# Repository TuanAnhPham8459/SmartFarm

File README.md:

<h1 align="center">Smart Farm</h1>

<p align="center">
  <b>Real-time farm monitoring: Raspberry Pi sensors → Cloud Firestore → Android app with live alerts</b>
</p>

---

## Overview

Smart Farm is an end-to-end IoT system that helps growers watch their environment remotely.
A Raspberry Pi 4 with a **custom sensor PCB** measures temperature, humidity, pressure, air
quality, light, and produce color, reads RFID tags, and shows status on a small OLED. Every
reading is uploaded to **Cloud Firestore**, and an **Android app** displays the data live,
charts history, and sends notifications when conditions go out of range.

Built by a team of four as our Computer Engineering Technology capstone at Humber College.

## Features

**Hardware & firmware (Raspberry Pi 4)**
- 🌡️ **Environment:** temperature, humidity, pressure, and gas/air quality (BME688)
- 💡 **Light:** ambient lux (VEML7700)
- 🍅 **Produce color classification:** GREEN / YELLOW / BROWN / RED with a calibration mode (OPT4048)
- 🏷️ **RFID:** ID-12LA reader on an I²C carrier board
- 🖥️ **On-device display:** SSD1305 128×32 OLED status screen, plus a GPIO LED indicator
- ☁️ **Cloud upload:** timestamped readings written to Firestore
- 🧵 **Reliable I²C:** one shared bus with a single lock across all devices, so threads never collide

**Android app**
- 🔐 Email and Google sign-in (Firebase Authentication), account profile with photo
- 📊 Live dashboard of the latest sensor readings
- 📈 History and analytics graphs (MPAndroidChart)
- 🚨 Threshold alerts with push notifications and a cooldown so you aren't spammed
- 🎛️ Control panel for device actions (irrigation pump, fan, light, auto mode)
- 🌙 Light and dark themes, French translation, unit switching, landscape layouts
- 💬 In-app feedback and help pages
- ✅ Unit tests (JUnit, Robolectric) and UI tests (Espresso)

## How it works

```mermaid
flowchart LR
    subgraph PI["Raspberry Pi 4 + custom PCB"]
        S1[BME688<br/>env + air quality]
        S2[VEML7700<br/>light]
        S3[OPT4048<br/>color]
        S4[ID-12LA<br/>RFID]
        FW[Python firmware<br/>shared I²C bus]
        OLED[SSD1305 OLED<br/>+ GPIO LED]
        S1 & S2 & S3 & S4 -->|I²C / Qwiic| FW
        FW --> OLED
    end
    FW -->|readings| FS[(Cloud Firestore)]
    FS -->|live updates| APP[Android app]
    APP -->|controls| FS
    APP --> N[Push alerts]
```

Firestore layout used by the firmware and the app:

```
sensor_data/{deviceId}/readings/{timestamp}   ← sensor readings from the Pi
devices/…                                      ← registered devices and controls
history/…                                      ← alert history
feedback/…                                     ← in-app feedback
```

## Tech stack

| Layer | Tools |
|---|---|
| Mobile app | Java, Android SDK (min SDK 31), Material Components, MPAndroidChart, Glide |
| Cloud | Firebase Authentication, Cloud Firestore, Firebase Storage |
| Firmware | Python 3, Adafruit Blinka / CircuitPython libraries, smbus2, Pillow |
| Hardware | Raspberry Pi 4, BME688, VEML7700, OPT4048, ID-12LA RFID, SSD1305 OLED, Qwiic |
| Design | KiCad (custom PCB), laser-cut enclosure (SVG) |
| Testing | JUnit, Robolectric, Espresso |

## Repository structure

```
SmartFarm/
├── SmartFarmModule/      Android app (Java)
│   └── src/main/java/ca/iot/innovators/smart/farm/
│       ├── firestore/    data managers for sensors, devices, alerts
│       ├── ui/           dashboard, control panel, settings, help, feedback
│       ├── alert/        alert list and notifications
│       ├── history/      analytics graphs
│       └── login/ signup/ profile/
├── hardware/
│   ├── firmware/         Raspberry Pi Python scripts
│   ├── pcb/              KiCad schematic and board files
│   └── *.svg, *.docx     enclosure drawings, bill of materials, build reports
├── docs/                 project deliverables 1–5 (PDF)
├── system/               weekly course status reports
└── privacy-policy/       app privacy policy and account deletion pages
```

## Getting started

### Raspberry Pi firmware

```bash
# 1. Enable I²C:  sudo raspi-config → Interface Options → I2C
# 2. Install dependencies
pip3 install adafruit-blinka adafruit-circuitpython-bme680 \
             adafruit-circuitpython-veml7700 adafruit-circuitpython-ssd1305 \
             adafruit-circuitpython-opt4048 smbus2 pillow google-cloud-firestore
# 3. Check that the sensors are detected
i2cdetect -y 1        # expect 0x10, 0x15, 0x3C, 0x77 (and the OPT4048)
# 4. Run
cd hardware/firmware
python3 pcb_sensors_color_oled_firestore.py             # everything
python3 pcb_sensors_color_oled_firestore.py calibrate   # color calibration only
```

You'll need a Firebase service account key on the Pi for the Firestore upload.

### Android app

1. Open the project in **Android Studio**.
2. Add your own `google-services.json` from a Firebase project to `SmartFarmModule/`.
3. Build and run on a device or emulator running Android 12 (API 31) or later.

## Project documents

- 📄 [Deliverables 1–5](docs/)
- 🪧 [Project poster](hardware/SmartFarm_poster.pdf)
- 🔌 [PCB design files](hardware/pcb/)
- 🧾 [Bill of materials](hardware/Smart%20Farm%20-%20BoM.docx)

## Team

| Member | Focus |
|---|---|
| Chau Vi Cuong Nguyen | Hardware, firmware, PCB design |
| Hoang Tran | Hardware, firmware, RFID reader |
| Truong An Nguyen | Hardware, firmware, OPT4048 color sensing |
| **Tuan Anh Pham** | Hardware, firmware, sensor integration |

### My contribution (Tuan Anh Pham)
- Merged the PCB sensor script and the OPT4048 color-classification script into one program
  (`pcb_sensors_color_oled_firestore.py`) that drives every sensor, the OLED, and the Firestore upload
- Diagnosed and fixed a bug where the RFID reader status stored in Firestore didn't match the reader's real state
- Wrote my individual hardware report with build instructions for the Raspberry Pi platform

> This repository is my fork of the team's capstone project.

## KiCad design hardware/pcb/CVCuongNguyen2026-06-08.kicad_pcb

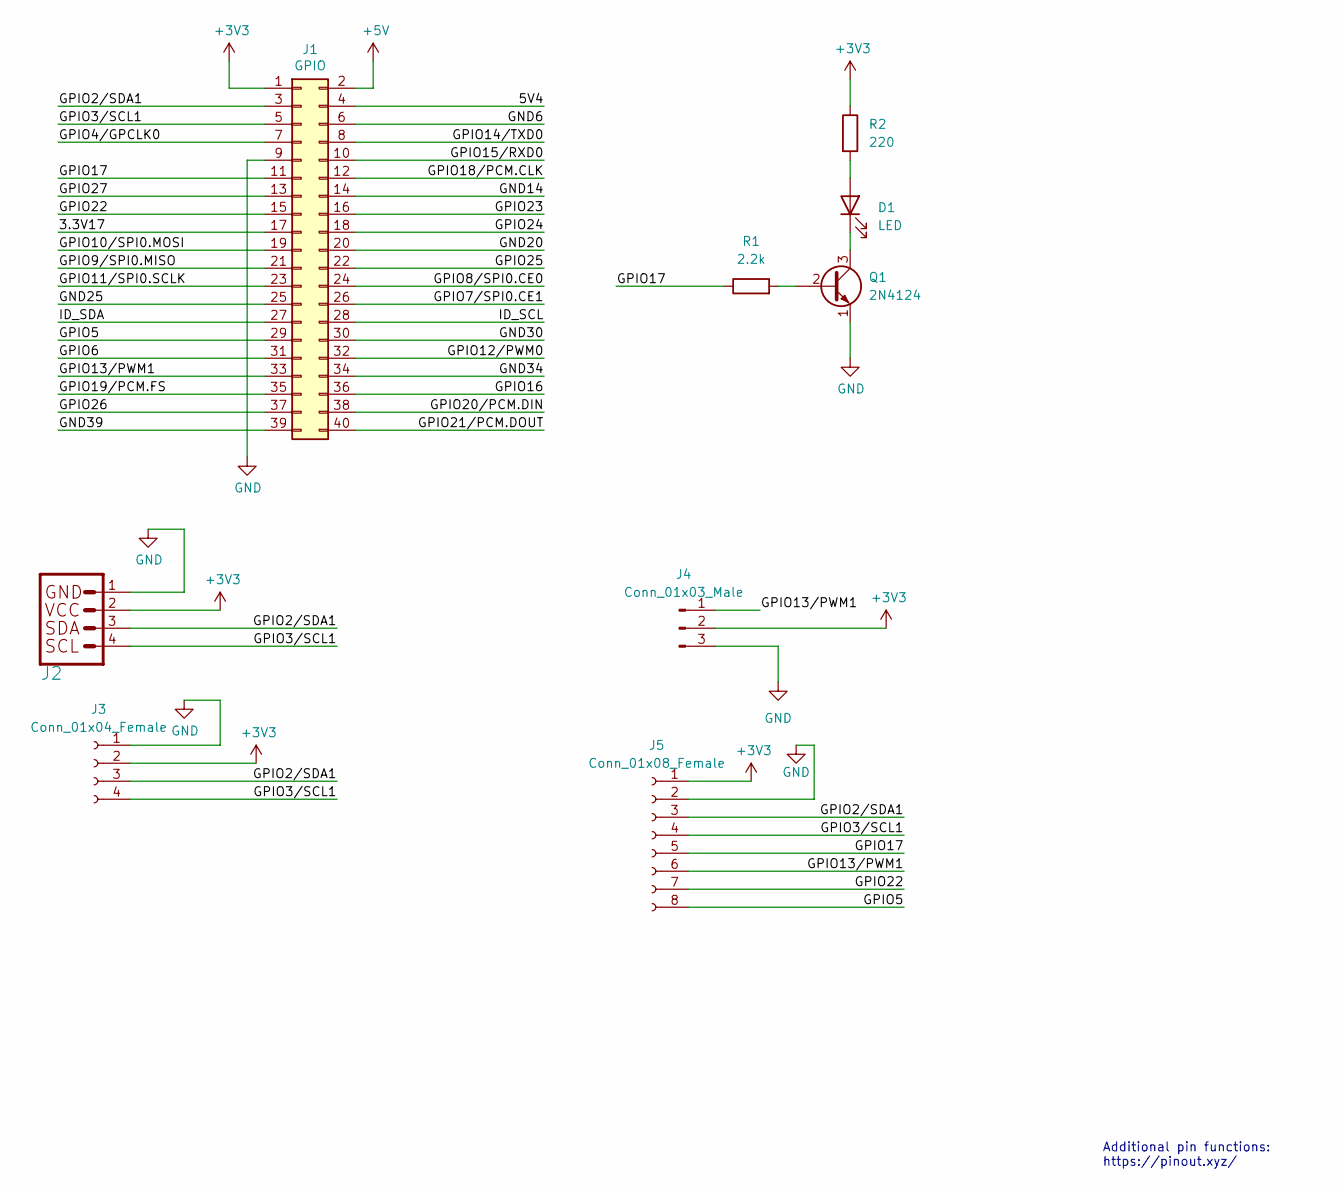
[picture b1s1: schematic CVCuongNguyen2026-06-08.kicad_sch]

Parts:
D1: LED; LED_D5.0mm_Horizontal_O1.27mm_Z3.0mm
J1: GPIO; PinSocket_2x20_P2.54mm_Vertical
J2: Qwiic Right Angle; PinSocket_1x04_P2.00mm_Horizontal
J3: Conn_01x04_Female; PinSocket_1x04_P2.54mm_Horizontal
J4: Conn_01x03_Male; PinHeader_1x03_P2.54mm_Horizontal
J5: Conn_01x08_Female; PinSocket_1x08_P2.54mm_Horizontal
Q1: 2N4124; TO-92_Inline_Wide
R1: 2.2k; R_Axial_DIN0207_L6.3mm_D2.5mm_P15.24mm_Horizontal
R2: 220; R_Axial_DIN0207_L6.3mm_D2.5mm_P15.24mm_Horizontal

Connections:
+3V3: J1.1, J2.2, J3.2, J4.2, J5.1, R2.1
+5V: J1.2
/3.3V17: J1.17
/5V4: J1.4
/GND6: J1.6
/GND14: J1.14
/GND20: J1.20
/GND25: J1.25
/GND30: J1.30
/GND34: J1.34
/GND39: J1.39
/GPIO2/SDA1: J1.3, J2.3, J3.3, J5.3
/GPIO3/SCL1: J1.5, J2.4, J3.4, J5.4
/GPIO4/GPCLK0: J1.7
/GPIO5: J1.29, J5.8
/GPIO6: J1.31
/GPIO7/SPI0.CE1: J1.26
/GPIO8/SPI0.CE0: J1.24
/GPIO9/SPI0.MISO: J1.21
/GPIO10/SPI0.MOSI: J1.19
/GPIO11/SPI0.SCLK: J1.23
/GPIO12/PWM0: J1.32
/GPIO13/PWM1: J1.33, J4.1, J5.6
/GPIO14/TXD0: J1.8
/GPIO15/RXD0: J1.10
/GPIO16: J1.36
/GPIO17: J1.11, J5.5, R1.1
/GPIO18/PCM.CLK: J1.12
/GPIO19/PCM.FS: J1.35
/GPIO20/PCM.DIN: J1.38
/GPIO21/PCM.DOUT: J1.40
/GPIO22: J1.15, J5.7
/GPIO23: J1.16
/GPIO24: J1.18
/GPIO25: J1.22
/GPIO26: J1.37
/GPIO27: J1.13
/ID_SCL: J1.28
/ID_SDA: J1.27
GND: J1.9, J2.1, J3.1, J4.3, J5.2, Q1.1 (E)
unnamed: D1.2 (A), R2.2
unnamed: D1.1 (K), Q1.3 (C)
unnamed: Q1.2 (B), R1.2

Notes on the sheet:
Additional pin functions: https://pinout.xyz/

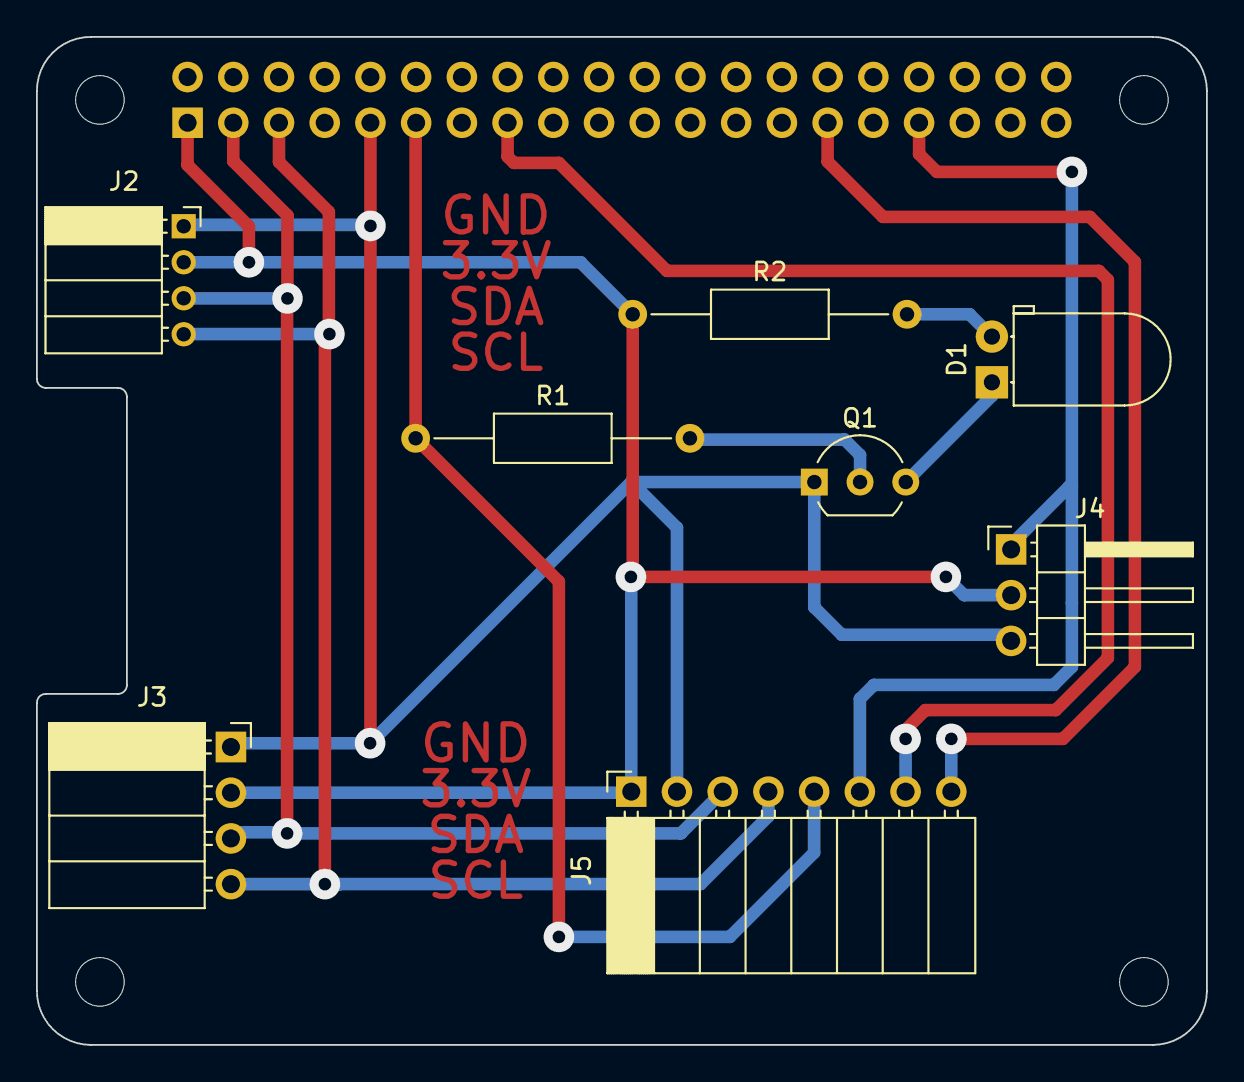
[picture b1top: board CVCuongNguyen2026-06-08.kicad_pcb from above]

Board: 2 copper layers, 65.0 x 56.0 mm, 13 parts (1 on the bottom side), 11 nets.

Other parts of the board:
MH1, MH2, MH3, MH4: MountingHole_2.7mm_M2.5
